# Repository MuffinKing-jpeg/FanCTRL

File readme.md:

# FanCTRL

Yet another fan controller. Has muxing capabilities. Can convert DC input to pwm output or vice versa.  

<center style="font-size: 40px;">WIP</center>

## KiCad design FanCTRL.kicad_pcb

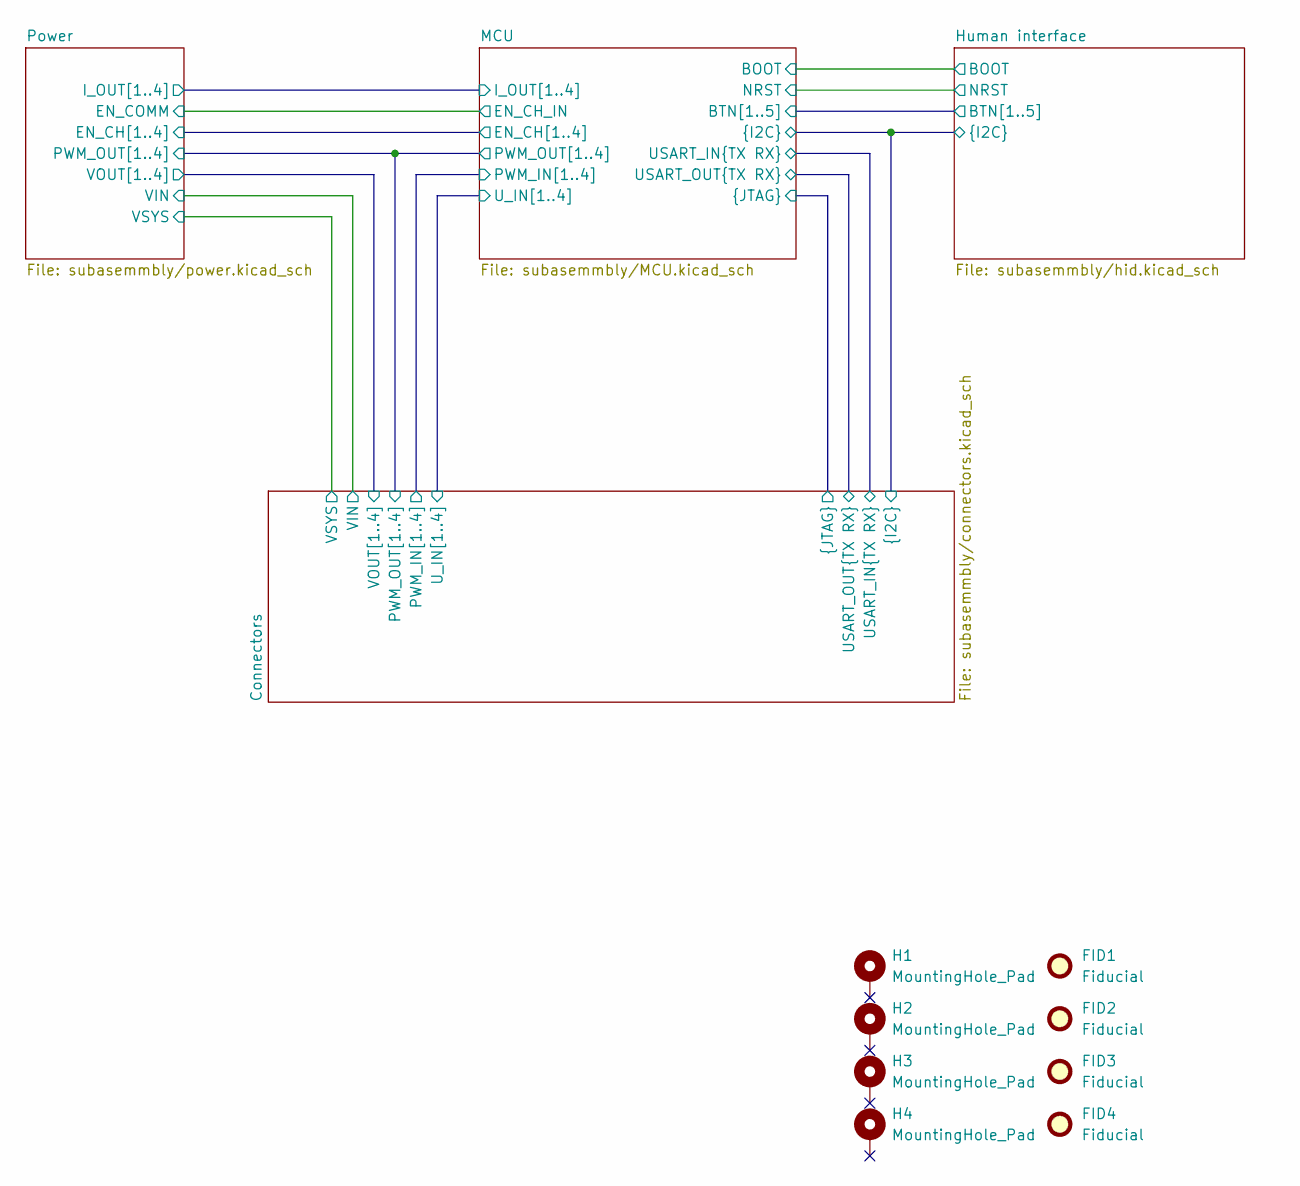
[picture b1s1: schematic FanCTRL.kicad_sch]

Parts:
FID1, FID2, FID3, FID4: Fiducial; Fiducial_1mm_Mask3mm
H1, H2, H3, H4: MountingHole_Pad; MountingHole_3.2mm_M3_ISO7380_Pad

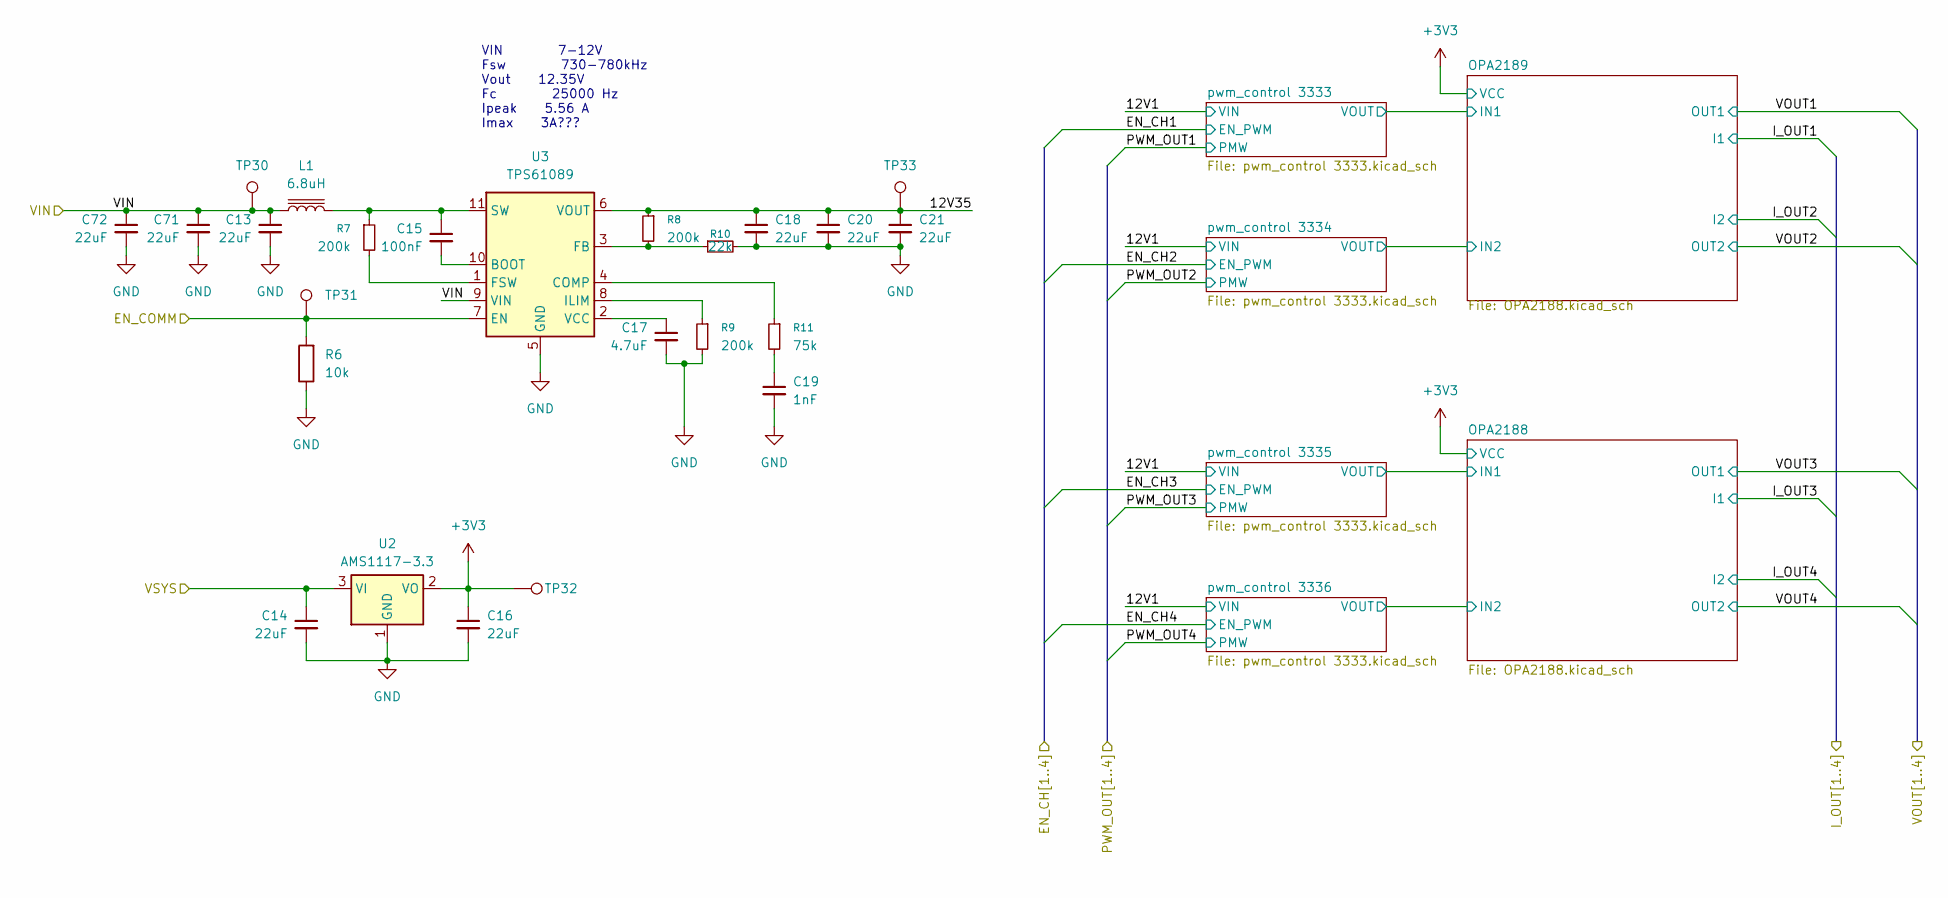
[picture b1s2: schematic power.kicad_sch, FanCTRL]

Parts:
C13, C14, C16, C18, C20, C21, C71, C72: 22uF; C_0805_2012Metric
C15: 100nF; C_0603_1608Metric
C17: 4.7uF; C_0603_1608Metric
C19: 1nF; C_0402_1005Metric
L1: 6.8uH; L_Changjiang_FXL0630; LCSC C167221
R6: 10k; R_0603_1608Metric
R7, R8, R9: 200k; R_0402_1005Metric
R10: 22k; R_0402_1005Metric
R11: 75k; R_0402_1005Metric
TP30: VIN; TestPoint_Pad_D1.0mm
TP31: EN_12V; TestPoint_THTPad_D1.0mm_Drill0.5mm
TP32: 3V3; TestPoint_THTPad_D1.0mm_Drill0.5mm
TP33: 12V35; TestPoint_THTPad_D2.0mm_Drill1.0mm
U2: AMS1117-3.3; SOT-223-3_TabPin2
U3: TPS61089; Texas_VQFN-RNR0011A-11

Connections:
+3V3: C16.1, TP32.1 (1_1), U2.2 (VO); also elsewhere on the board
/Connectors/VIN: C13.1, C71.1, C72.1, L1.1, TP30.1 (1_1), U3.9 (VIN); also elsewhere on the board
/Connectors/VSYS: C14.1, U2.3 (VI); also elsewhere on the board
/MCU/EN_CH_IN: R6.2, TP31.1 (1_1), U3.7 (EN); also elsewhere on the board
/Power/12V35: C18.1, C20.1, C21.1, R8.1, TP33.1 (1_1), U3.6 (VOUT)
GND: C13.2, C14.2, C16.2, C17.2, C18.2, C19.2, C20.2, C21.2, C71.2, C72.2, R6.1, R9.2, R10.2, U2.1 (GND), U3.5 (GND); also elsewhere on the board
unnamed: C19.1, R11.2
unnamed: C15.2, U3.10 (BOOT)
unnamed: R11.1, U3.4 (COMP)
unnamed: R8.2, R10.1, U3.3 (FB)
unnamed: R7.2, U3.1 (FSW)
unnamed: R9.1, U3.8 (ILIM)
unnamed: C15.1, L1.2, R7.1, U3.11 (SW)
unnamed: C17.1, U3.2 (VCC)

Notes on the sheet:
VIN 7-12V Fsw 730-780kHz Vout 12.35V Fc 25000 Hz Ipeak 5.56 A Imax 3A???

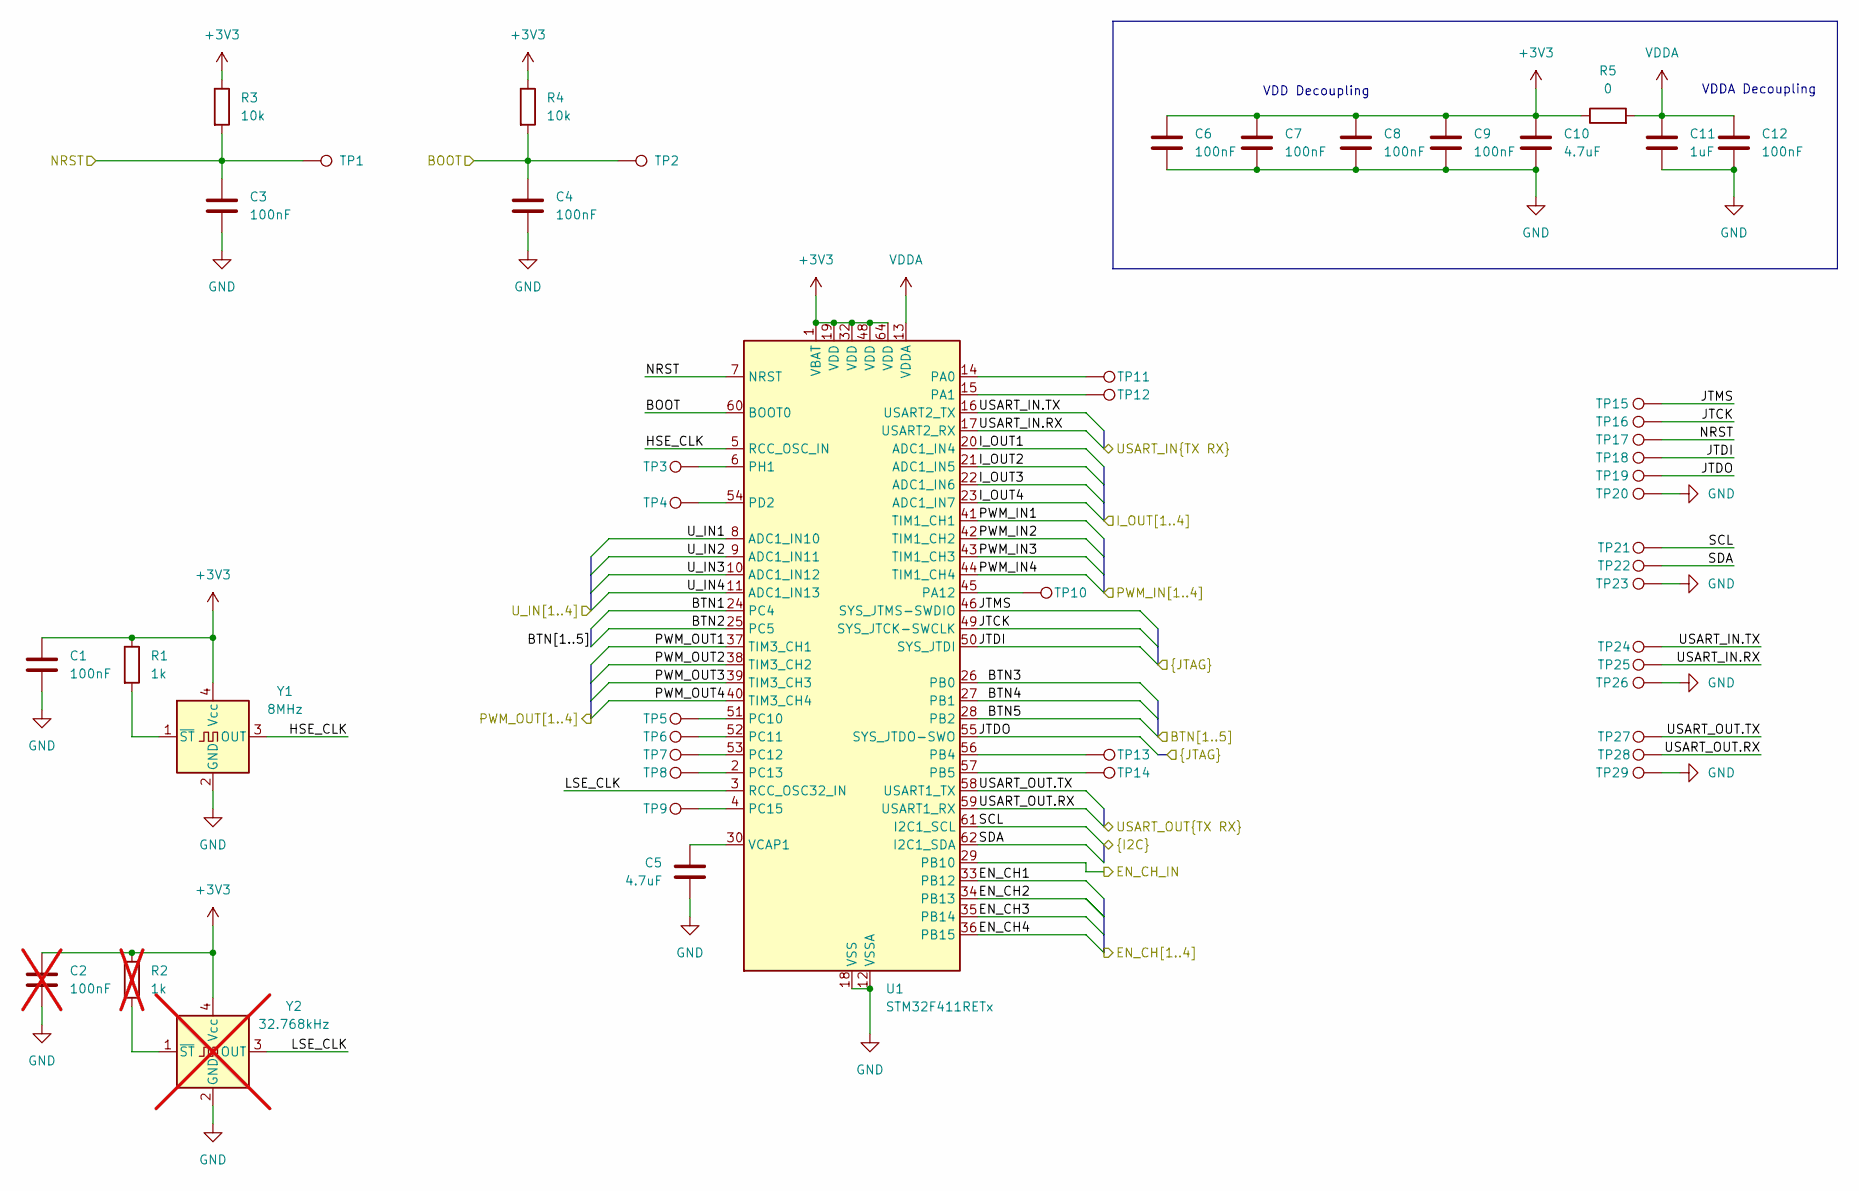
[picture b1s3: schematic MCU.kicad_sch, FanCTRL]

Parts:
C1, C3, C4, C6, C7, C8, C9, C12: 100nF; C_0603_1608Metric
C2: 100nF; C_0603_1608Metric; not fitted
C5, C10: 4.7uF; C_0603_1608Metric
C11: 1uF; C_0603_1608Metric
R1: 1k; R_0603_1608Metric
R2: 1k; R_0603_1608Metric; not fitted
R3, R4: 10k; R_0603_1608Metric
R5: 0; R_0603_1608Metric_Pad0.98x0.95mm_HandSolder
TP1: NRST; TestPoint_THTPad_D1.0mm_Drill0.5mm
TP2: BOOT; TestPoint_THTPad_D1.0mm_Drill0.5mm
TP3, TP4, TP5, TP6, TP7, TP8, TP9, TP10, TP11, TP12, TP13, TP14: TestPoint; TestPoint_THTPad_D1.0mm_Drill0.5mm
TP15: JTMS; TestPoint_Pad_D1.0mm
TP16: JTCK; TestPoint_Pad_D1.0mm
TP17: NRST; TestPoint_Pad_D1.0mm
TP18: JTDI; TestPoint_Pad_D1.0mm
TP19: JTDO; TestPoint_Pad_D1.0mm
TP20: GND; TestPoint_Pad_D1.0mm
TP21: SCL; TestPoint_THTPad_D1.0mm_Drill0.5mm
TP22: SDA; TestPoint_THTPad_D1.0mm_Drill0.5mm
TP23, TP26, TP29: GND; TestPoint_THTPad_D1.0mm_Drill0.5mm
TP24, TP25, TP27, TP28: USART; TestPoint_THTPad_D1.0mm_Drill0.5mm
U1: STM32F411RETx; LQFP-64_10x10mm_P0.5mm
Y1: 8MHz; Oscillator_SMD_SeikoEpson_SG210-4Pin_2.5x2.0mm; LCSC C496696
Y2: 32.768kHz; Oscillator_SMD_SeikoEpson_SG210-4Pin_2.5x2.0mm; LCSC C496696; not fitted

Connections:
+3V3: C1.1, C2.1, C6.1, C7.1, C8.1, C9.1, C10.1, R1.1, R2.1, R3.1, R4.1, R5.1, U1.1 (VBAT), U1.19 (VDD), U1.32 (VDD), U1.48 (VDD), U1.64 (VDD), Y1.4 (Vcc), Y2.4 (Vcc); also elsewhere on the board
/Connectors/JTCK: TP16.1 (1_1), U1.49 (SYS_JTCK-SWCLK); also elsewhere on the board
/Connectors/JTDI: TP18.1 (1_1), U1.50 (SYS_JTDI); also elsewhere on the board
/Connectors/JTDO: TP19.1 (1_1), U1.55 (SYS_JTDO-SWO); also elsewhere on the board
/Connectors/JTMS: TP15.1 (1_1), U1.46 (SYS_JTMS-SWDIO); also elsewhere on the board
/Connectors/PWM_IN1: U1.41 (TIM1_CH1); also elsewhere on the board
/Connectors/PWM_IN2: U1.42 (TIM1_CH2); also elsewhere on the board
/Connectors/PWM_IN3: U1.43 (TIM1_CH3); also elsewhere on the board
/Connectors/PWM_IN4: U1.44 (TIM1_CH4); also elsewhere on the board
/Connectors/PWM_OUT1: U1.37 (TIM3_CH1); also elsewhere on the board
/Connectors/PWM_OUT2: U1.38 (TIM3_CH2); also elsewhere on the board
/Connectors/PWM_OUT3: U1.39 (TIM3_CH3); also elsewhere on the board
/Connectors/PWM_OUT4: U1.40 (TIM3_CH4); also elsewhere on the board
/Connectors/SCL: TP21.1 (1_1), U1.61 (I2C1_SCL); also elsewhere on the board
/Connectors/SDA: TP22.1 (1_1), U1.62 (I2C1_SDA); also elsewhere on the board
/Connectors/USART_IN.RX: TP25.1 (1_1), U1.17 (USART2_RX); also elsewhere on the board
/Connectors/USART_IN.TX: TP24.1 (1_1), U1.16 (USART2_TX); also elsewhere on the board
/Connectors/USART_OUT.RX: TP28.1 (1_1), U1.59 (USART1_RX); also elsewhere on the board
/Connectors/USART_OUT.TX: TP27.1 (1_1), U1.58 (USART1_TX); also elsewhere on the board
/Connectors/U_IN1: U1.8 (ADC1_IN10); also elsewhere on the board
/Connectors/U_IN2: U1.9 (ADC1_IN11); also elsewhere on the board
/Connectors/U_IN3: U1.10 (ADC1_IN12); also elsewhere on the board
/Connectors/U_IN4: U1.11 (ADC1_IN13); also elsewhere on the board
/MCU/BOOT: C4.1, R4.2, TP2.1 (1_1), U1.60 (BOOT0); also elsewhere on the board
/MCU/BTN1: U1.24 (PC4); also elsewhere on the board
/MCU/BTN2: U1.25 (PC5); also elsewhere on the board
/MCU/BTN3: U1.26 (PB0); also elsewhere on the board
/MCU/BTN4: U1.27 (PB1); also elsewhere on the board
/MCU/BTN5: U1.28 (PB2); also elsewhere on the board
/MCU/EN_CH1: U1.33 (PB12); also elsewhere on the board
/MCU/EN_CH2: U1.34 (PB13); also elsewhere on the board
/MCU/EN_CH3: U1.35 (PB14); also elsewhere on the board
/MCU/EN_CH4: U1.36 (PB15); also elsewhere on the board
/MCU/EN_CH_IN: U1.29 (PB10); also elsewhere on the board
/MCU/HSE_CLK: U1.5 (RCC_OSC_IN), Y1.3 (OUT)
/MCU/I_OUT1: U1.20 (ADC1_IN4); also elsewhere on the board
/MCU/I_OUT2: U1.21 (ADC1_IN5); also elsewhere on the board
/MCU/I_OUT3: U1.22 (ADC1_IN6); also elsewhere on the board
/MCU/I_OUT4: U1.23 (ADC1_IN7); also elsewhere on the board
/MCU/LSE_CLK: U1.3 (RCC_OSC32_IN), Y2.3 (OUT)
/MCU/NRST: C3.1, R3.2, TP1.1 (1_1), TP17.1 (1_1), U1.7 (NRST); also elsewhere on the board
GND: C1.2, C2.2, C3.2, C4.2, C5.2, C6.2, C7.2, C8.2, C9.2, C10.2, C11.2, C12.2, TP20.1 (1_1), TP23.1 (1_1), TP26.1 (1_1), TP29.1 (1_1), U1.12 (VSSA), U1.18 (VSS), U1.31 (VSS), U1.47 (VSS), U1.63 (VSS), Y1.2 (GND), Y2.2 (GND); also elsewhere on the board
unnamed: TP11.1 (1_1), U1.14 (PA0)
unnamed: TP12.1 (1_1), U1.15 (PA1)
unnamed: TP10.1 (1_1), U1.45 (PA12)
unnamed: TP13.1 (1_1), U1.56 (PB4)
unnamed: TP14.1 (1_1), U1.57 (PB5)
unnamed: TP5.1 (1_1), U1.51 (PC10)
unnamed: TP6.1 (1_1), U1.52 (PC11)
unnamed: TP7.1 (1_1), U1.53 (PC12)
unnamed: TP8.1 (1_1), U1.2 (PC13)
unnamed: TP9.1 (1_1), U1.4 (PC15)
unnamed: TP4.1 (1_1), U1.54 (PD2)
unnamed: TP3.1 (1_1), U1.6 (PH1)
unnamed: C5.1, U1.30 (VCAP1)
unnamed: R1.2, Y1.1 (~ST)
unnamed: R2.2, Y2.1 (~ST)
VDDA: C11.1, C12.1, R5.2, U1.13 (VDDA)

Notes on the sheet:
VDDA Decoupling
VDD Decoupling

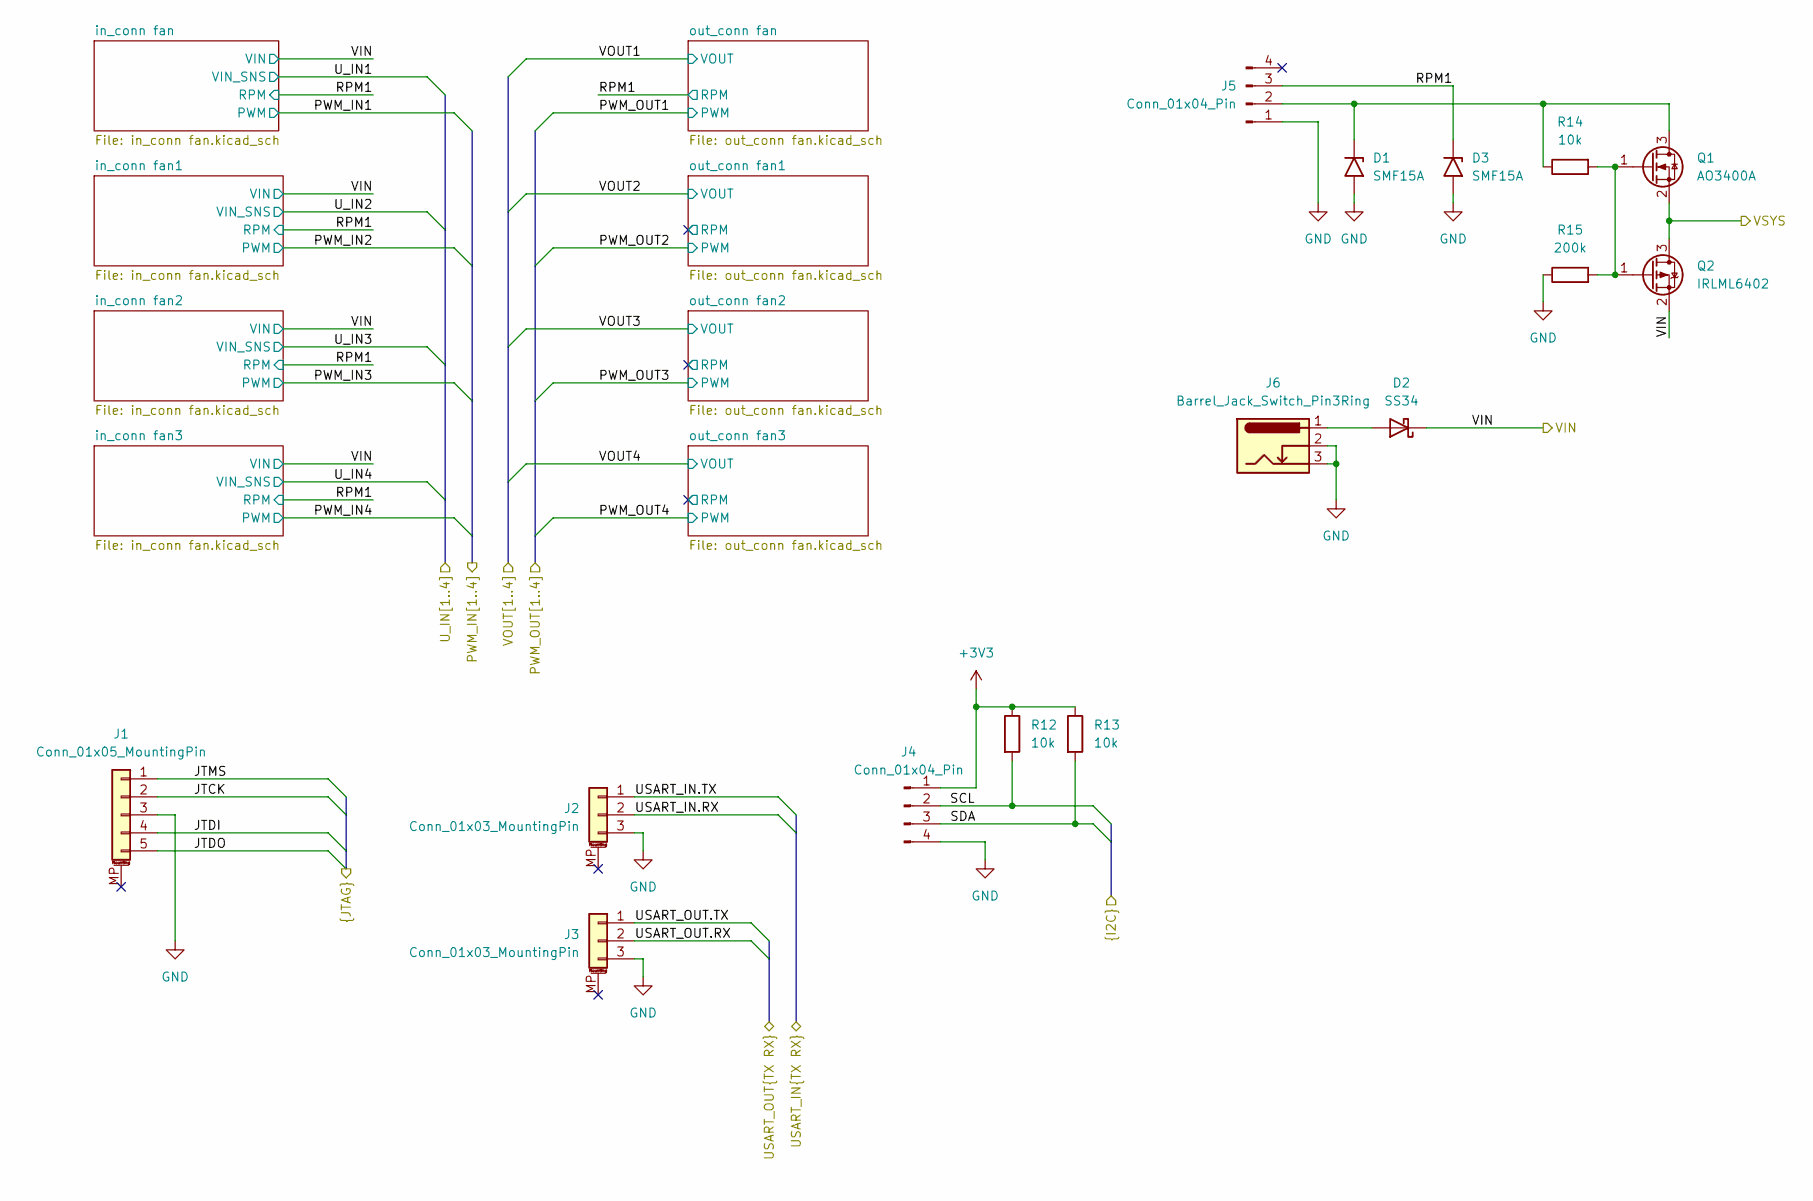
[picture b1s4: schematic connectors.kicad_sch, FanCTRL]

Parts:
D1, D3: SMF15A; D_SMF
D2: SS34; D_SMA
J1: Conn_01x05_MountingPin; Molex_PicoBlade_53261-0571_1x05-1MP_P1.25mm_Horizontal
J2, J3: Conn_01x03_MountingPin; Molex_PicoBlade_53261-0371_1x03-1MP_P1.25mm_Horizontal
J4: Conn_01x04_Pin; JST_EH_S4B-EH_1x04_P2.50mm_Horizontal
J5: Conn_01x04_Pin; FanPinHeader_1x04_P2.54mm_Vertical
J6: Barrel_Jack_Switch_Pin3Ring; BarrelJack_GCT_DCJ200-10-A_Horizontal
Q1: AO3400A; SOT-23
Q2: IRLML6402; SOT-23
R12, R13, R14: 10k; R_0603_1608Metric
R15: 200k; R_0402_1005Metric

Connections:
+3V3: J4.1, R12.1, R13.1; also elsewhere on the board
/Connectors/JTCK: J1.2; also elsewhere on the board
/Connectors/JTDI: J1.4; also elsewhere on the board
/Connectors/JTDO: J1.5; also elsewhere on the board
/Connectors/JTMS: J1.1; also elsewhere on the board
/Connectors/RPM1: D3.1 (A1), J5.3; also elsewhere on the board
/Connectors/SCL: J4.2, R12.2; also elsewhere on the board
/Connectors/SDA: J4.3, R13.2; also elsewhere on the board
/Connectors/USART_IN.RX: J2.2; also elsewhere on the board
/Connectors/USART_IN.TX: J2.1; also elsewhere on the board
/Connectors/USART_OUT.RX: J3.2; also elsewhere on the board
/Connectors/USART_OUT.TX: J3.1; also elsewhere on the board
/Connectors/VIN: D2.1 (K), Q2.2 (S); also elsewhere on the board
/Connectors/VSYS: Q1.2 (S), Q2.3 (D); also elsewhere on the board
GND: D1.2 (A2), D3.2 (A2), J1.3, J2.3, J3.3, J4.4, J5.1, J6.2, J6.3, R15.1; also elsewhere on the board
unnamed: D1.1 (A1), J5.2, Q1.3 (D), R14.1
unnamed: D2.2 (A), J6.1
unnamed: Q1.1 (G), Q2.1 (G), R14.2, R15.2

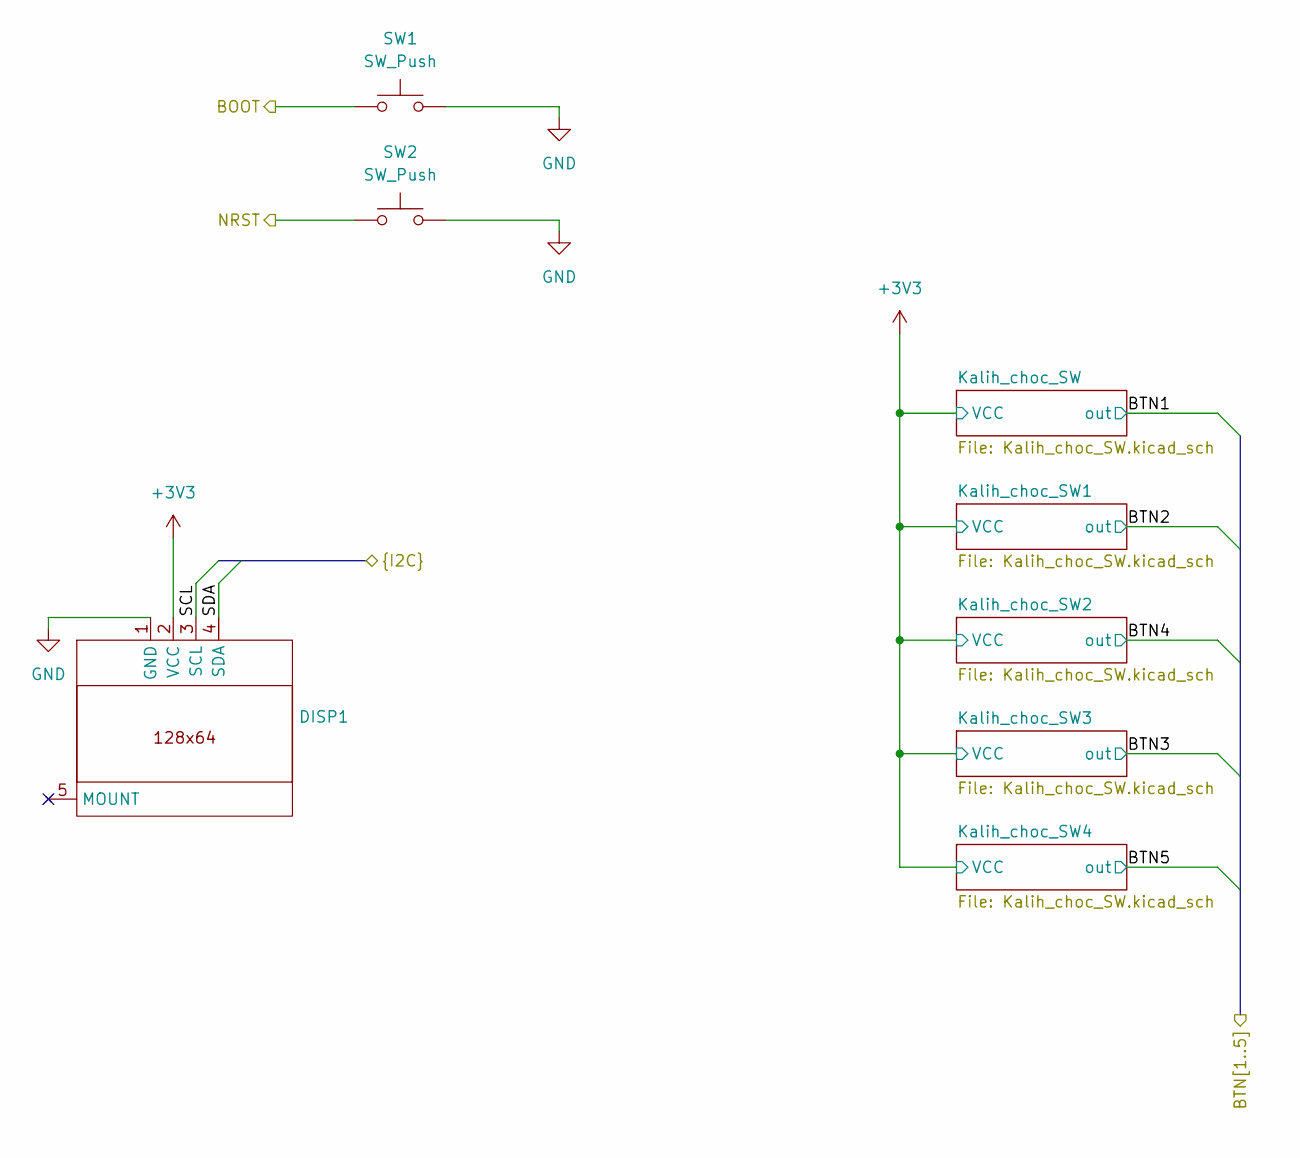
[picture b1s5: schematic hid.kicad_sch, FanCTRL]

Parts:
DISP1: OLED_Module_I2C_WeAct
SW1, SW2: SW_Push; SW_SPST_PTS810

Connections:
+3V3: DISP1.2 (VCC); also elsewhere on the board
/Connectors/SCL: DISP1.3 (SCL); also elsewhere on the board
/Connectors/SDA: DISP1.4 (SDA); also elsewhere on the board
/MCU/BOOT: SW1.1; also elsewhere on the board
/MCU/NRST: SW2.1; also elsewhere on the board
GND: DISP1.1 (GND), SW1.2, SW2.2; also elsewhere on the board

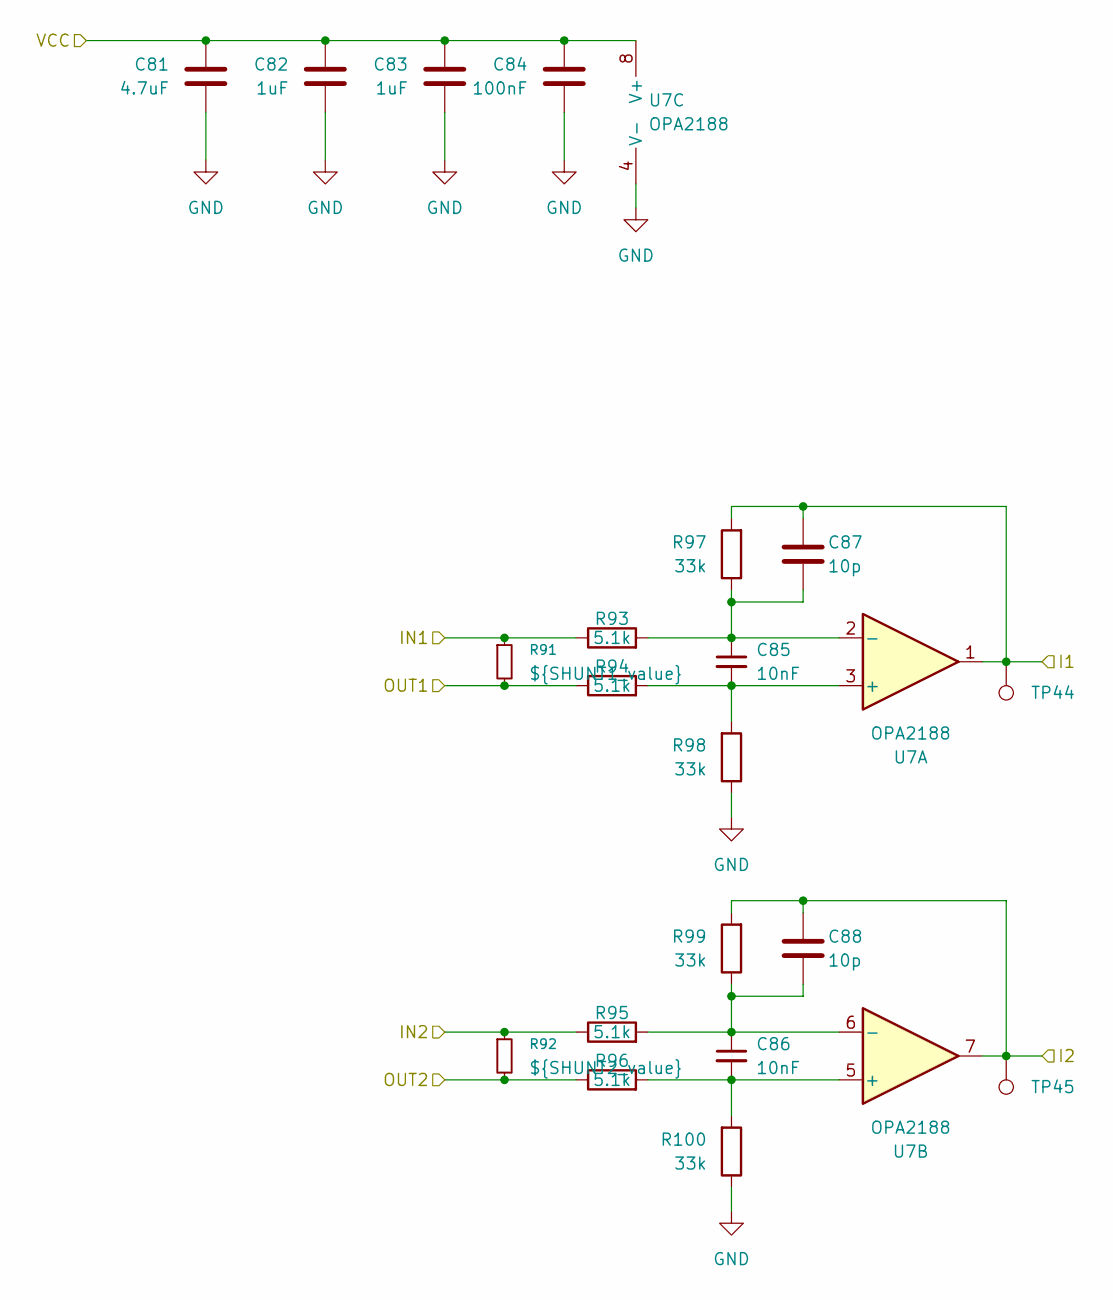
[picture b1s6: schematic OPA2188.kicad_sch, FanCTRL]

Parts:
C81: 4.7uF; C_0603_1608Metric
C82, C83: 1uF; C_0603_1608Metric
C84: 100nF; C_0603_1608Metric
C85, C86: 10nF; C_0402_1005Metric
C87, C88: 10p; C_0402_1005Metric
R91: ${SHUNT1_value}; R_2512_6332Metric; LCSC C49164952
R92: ${SHUNT2_value}; R_2512_6332Metric; LCSC C49164952
R93, R94, R95, R96: 5.1k; R_0402_1005Metric
R97, R98, R99, R100: 33k; R_0402_1005Metric
TP44, TP45: I_OUT; TestPoint_Pad_D1.0mm
U7: OPA2188; SOIC-8_3.9x4.9mm_P1.27mm

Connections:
+3V3: C81.1, C82.1, C83.1, C84.1, U7.8 (V+); also elsewhere on the board
/Connectors/VOUT1: R91.2, R94.1; also elsewhere on the board
/Connectors/VOUT2: R92.2, R96.1; also elsewhere on the board
/MCU/I_OUT1: C87.1, R97.2, TP44.1 (1_1), U7.1; also elsewhere on the board
/MCU/I_OUT2: C88.1, R99.2, TP45.1 (1_1), U7.7; also elsewhere on the board
/Power/OPA2189/IN1: R91.1, R93.1; also elsewhere on the board
/Power/OPA2189/IN2: R92.1, R95.1; also elsewhere on the board
GND: C81.2, C82.2, C83.2, C84.2, R98.1, R100.1, U7.4 (V-); also elsewhere on the board
unnamed: C85.2, R94.2, R98.2, U7.3 (+)
unnamed: C85.1, C87.2, R93.2, R97.1, U7.2 (-)
unnamed: C86.2, R96.2, R100.2, U7.5 (+)
unnamed: C86.1, C88.2, R95.2, R99.1, U7.6 (-)

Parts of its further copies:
C73: 4.7uF; C_0603_1608Metric
C74, C75: 1uF; C_0603_1608Metric
C76: 100nF; C_0603_1608Metric
C77, C78: 10nF; C_0402_1005Metric
C79, C80: 10p; C_0402_1005Metric
R83, R84, R85, R86: 5.1k; R_0402_1005Metric
R87, R88, R89, R90: 33k; R_0402_1005Metric
TP42, TP43: I_OUT; TestPoint_Pad_D1.0mm
U6: OPA2188; SOIC-8_3.9x4.9mm_P1.27mm

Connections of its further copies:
+3V3: C73.1, C74.1, C75.1, C76.1, U6.8 (V+); also elsewhere on the board
/Connectors/VOUT3: R84.1; also elsewhere on the board
/Connectors/VOUT4: R86.1; also elsewhere on the board
/MCU/I_OUT3: C79.1, R87.2, TP42.1 (1_1), U6.1; also elsewhere on the board
/MCU/I_OUT4: C80.1, R89.2, TP43.1 (1_1), U6.7; also elsewhere on the board
/Power/OPA2188/IN1: R83.1; also elsewhere on the board
/Power/OPA2188/IN2: R85.1; also elsewhere on the board
GND: C73.2, C74.2, C75.2, C76.2, R88.1, R90.1, U6.4 (V-); also elsewhere on the board
unnamed: C77.2, R84.2, R88.2, U6.3 (+)
unnamed: C77.1, C79.2, R83.2, R87.1, U6.2 (-)
unnamed: C78.2, R86.2, R90.2, U6.5 (+)
unnamed: C78.1, C80.2, R85.2, R89.1, U6.6 (-)

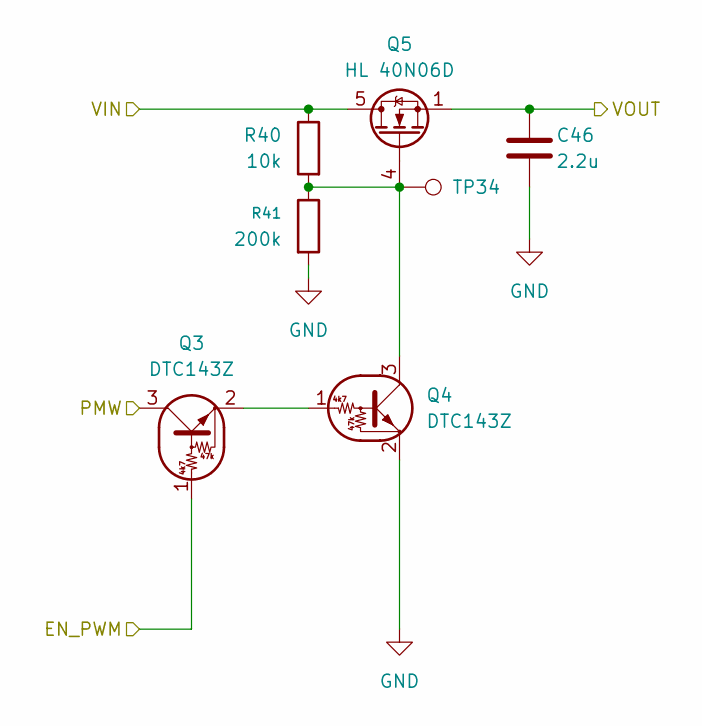
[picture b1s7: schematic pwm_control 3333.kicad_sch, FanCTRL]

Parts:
C46: 2.2u; C_0603_1608Metric
Q3, Q4: DTC143Z; SC-59
Q5: HL 40N06D; PowerDI3333-8; LCSC C7543836
R40: 10k; R_0603_1608Metric
R41: 200k; R_0402_1005Metric
TP34: OUT_GATE; TestPoint_Pad_D1.0mm

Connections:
/Connectors/PWM_OUT1: Q3.3 (C); also elsewhere on the board
/MCU/EN_CH1: Q3.1 (B); also elsewhere on the board
/Power/12V1: Q5.5 (D), R40.1; also elsewhere on the board
/Power/OPA2189/IN1: C46.1, Q5.1 (S), Q5.2 (S), Q5.3 (S); also elsewhere on the board
GND: C46.2, Q4.2 (E), R41.2; also elsewhere on the board
unnamed: Q3.2 (E), Q4.1 (B)
unnamed: Q4.3 (C), Q5.4 (G), R40.2, R41.1, TP34.1 (1_1)

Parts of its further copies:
C47, C48, C49: 2.2u; C_0603_1608Metric
Q6, Q7, Q9, Q10, Q12, Q13: DTC143Z; SC-59
Q8, Q11, Q14: HL 40N06D; PowerDI3333-8; LCSC C7543836
R42, R44, R46: 10k; R_0603_1608Metric
R43, R45, R47: 200k; R_0402_1005Metric
TP35, TP36, TP37: OUT_GATE; TestPoint_Pad_D1.0mm

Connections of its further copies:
/Connectors/PWM_OUT2: Q6.3 (C); also elsewhere on the board
/Connectors/PWM_OUT3: Q9.3 (C); also elsewhere on the board
/Connectors/PWM_OUT4: Q12.3 (C); also elsewhere on the board
/MCU/EN_CH2: Q6.1 (B); also elsewhere on the board
/MCU/EN_CH3: Q9.1 (B); also elsewhere on the board
/MCU/EN_CH4: Q12.1 (B); also elsewhere on the board
/Power/12V1: Q8.5 (D), Q11.5 (D), Q14.5 (D), R42.1, R44.1, R46.1; also elsewhere on the board
/Power/OPA2188/IN1: C48.1, Q11.1 (S), Q11.2 (S), Q11.3 (S); also elsewhere on the board
/Power/OPA2188/IN2: C49.1, Q14.1 (S), Q14.2 (S), Q14.3 (S); also elsewhere on the board
/Power/OPA2189/IN2: C47.1, Q8.1 (S), Q8.2 (S), Q8.3 (S); also elsewhere on the board
GND: C47.2, C48.2, C49.2, Q7.2 (E), Q10.2 (E), Q13.2 (E), R43.2, R45.2, R47.2; also elsewhere on the board
unnamed: Q6.2 (E), Q7.1 (B)
unnamed: Q7.3 (C), Q8.4 (G), R42.2, R43.1, TP35.1 (1_1)
unnamed: Q9.2 (E), Q10.1 (B)
unnamed: Q10.3 (C), Q11.4 (G), R44.2, R45.1, TP36.1 (1_1)
unnamed: Q12.2 (E), Q13.1 (B)
unnamed: Q13.3 (C), Q14.4 (G), R46.2, R47.1, TP37.1 (1_1)

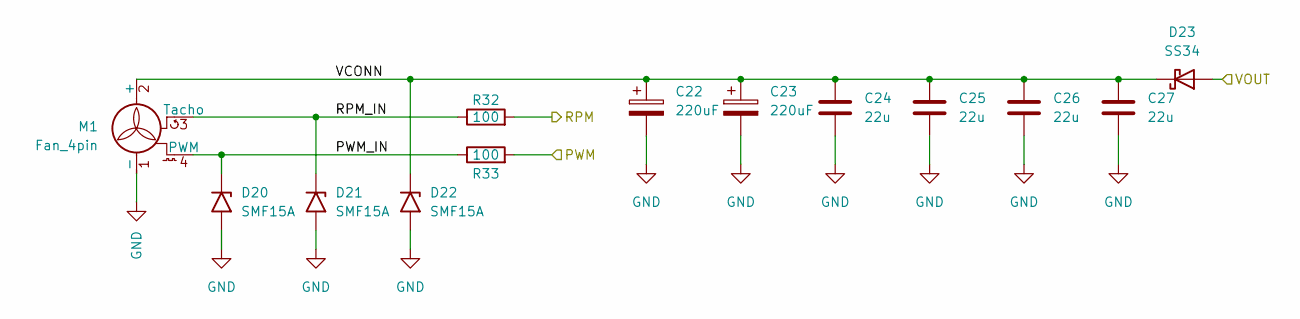
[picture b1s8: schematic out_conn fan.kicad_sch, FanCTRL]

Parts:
C22, C23: 220uF; CP_Radial_D8.0mm_P2.50mm; LCSC C107639
C24, C25, C26, C27: 22u; C_0805_2012Metric
D20, D21, D22: SMF15A; D_SMF
D23: SS34; D_SMA
M1: Fan_4pin; FanPinHeader_1x04_P2.54mm_Vertical
R32, R33: 100; R_0603_1608Metric

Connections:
/Connectors/PWM_OUT1: R33.2; also elsewhere on the board
/Connectors/RPM1: R32.2; also elsewhere on the board
/Connectors/VOUT1: D23.2 (A); also elsewhere on the board
/Connectors/out_conn fan/PWM_IN: D20.1 (A1), M1.4 (PWM), R33.1
/Connectors/out_conn fan/RPM_IN: D21.1 (A1), M1.3 (Tacho), R32.1
/Connectors/out_conn fan/VCONN: C22.1, C23.1, C24.1, C25.1, C26.1, C27.1, D22.1 (A1), D23.1 (K), M1.2 (+)
GND: C22.2, C23.2, C24.2, C25.2, C26.2, C27.2, D20.2 (A2), D21.2 (A2), D22.2 (A2), M1.1 (-); also elsewhere on the board

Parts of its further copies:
C28, C29, C34, C35, C40, C41: 220uF; CP_Radial_D8.0mm_P2.50mm; LCSC C107639
C30, C31, C32, C33, C36, C37, C38, C39, C42, C43, C44, C45: 22u; C_0805_2012Metric
D24, D25, D26, D28, D29, D30, D32, D33, D34: SMF15A; D_SMF
D27, D31, D35: SS34; D_SMA
M2, M3, M4: Fan_4pin; FanPinHeader_1x04_P2.54mm_Vertical
R34, R35, R36, R37, R38, R39: 100; R_0603_1608Metric

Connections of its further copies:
/Connectors/PWM_OUT2: R35.2; also elsewhere on the board
/Connectors/PWM_OUT3: R37.2; also elsewhere on the board
/Connectors/PWM_OUT4: R39.2; also elsewhere on the board
/Connectors/VOUT2: D27.2 (A); also elsewhere on the board
/Connectors/VOUT3: D31.2 (A); also elsewhere on the board
/Connectors/VOUT4: D35.2 (A); also elsewhere on the board
/Connectors/out_conn fan1/PWM_IN: D24.1 (A1), M2.4 (PWM), R35.1
/Connectors/out_conn fan1/RPM: R34.2
/Connectors/out_conn fan1/RPM_IN: D25.1 (A1), M2.3 (Tacho), R34.1
/Connectors/out_conn fan1/VCONN: C28.1, C29.1, C30.1, C31.1, C32.1, C33.1, D26.1 (A1), D27.1 (K), M2.2 (+)
/Connectors/out_conn fan2/PWM_IN: D28.1 (A1), M3.4 (PWM), R37.1
/Connectors/out_conn fan2/RPM: R36.2
/Connectors/out_conn fan2/RPM_IN: D29.1 (A1), M3.3 (Tacho), R36.1
/Connectors/out_conn fan2/VCONN: C34.1, C35.1, C36.1, C37.1, C38.1, C39.1, D30.1 (A1), D31.1 (K), M3.2 (+)
/Connectors/out_conn fan3/PWM_IN: D32.1 (A1), M4.4 (PWM), R39.1
/Connectors/out_conn fan3/RPM: R38.2
/Connectors/out_conn fan3/RPM_IN: D33.1 (A1), M4.3 (Tacho), R38.1
/Connectors/out_conn fan3/VCONN: C40.1, C41.1, C42.1, C43.1, C44.1, C45.1, D34.1 (A1), D35.1 (K), M4.2 (+)
GND: C28.2, C29.2, C30.2, C31.2, C32.2, C33.2, C34.2, C35.2, C36.2, C37.2, C38.2, C39.2, C40.2, C41.2, C42.2, C43.2, C44.2, C45.2, D24.2 (A2), D25.2 (A2), D26.2 (A2), D28.2 (A2), D29.2 (A2), D30.2 (A2), D32.2 (A2), D33.2 (A2), D34.2 (A2), M2.1 (-), M3.1 (-), M4.1 (-); also elsewhere on the board

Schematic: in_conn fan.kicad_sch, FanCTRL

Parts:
D4, D5, D6: SMF15A; D_SMF
D7: SS34; D_SMA
J7: Conn_01x04_Pin; FanPinHeader_1x04_P2.54mm_Vertical
R16: 75k; R_0402_1005Metric
R17: 22k; R_0402_1005Metric
R18, R19: 100; R_0603_1608Metric

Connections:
/Connectors/PWM_IN1: R19.2; also elsewhere on the board
/Connectors/RPM1: R18.2; also elsewhere on the board
/Connectors/U_IN1: R16.2, R17.1; also elsewhere on the board
/Connectors/VIN: D7.1 (K); also elsewhere on the board
/Connectors/in_conn fan/PWM_IN: D4.1 (A1), J7.4, R19.1
/Connectors/in_conn fan/RPM_IN: D5.1 (A1), J7.3, R18.1
/Connectors/in_conn fan/VCONN: D6.1 (A1), D7.2 (A), J7.2, R16.1
GND: D4.2 (A2), D5.2 (A2), D6.2 (A2), J7.1, R17.2; also elsewhere on the board

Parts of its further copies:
D8, D9, D10, D12, D13, D14, D16, D17, D18: SMF15A; D_SMF
D11, D15, D19: SS34; D_SMA
J8, J9, J10: Conn_01x04_Pin; FanPinHeader_1x04_P2.54mm_Vertical
R20, R24, R28: 75k; R_0402_1005Metric
R21, R25, R29: 22k; R_0402_1005Metric
R22, R23, R26, R27, R30, R31: 100; R_0603_1608Metric

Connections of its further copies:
/Connectors/PWM_IN2: R23.2; also elsewhere on the board
/Connectors/PWM_IN3: R27.2; also elsewhere on the board
/Connectors/PWM_IN4: R31.2; also elsewhere on the board
/Connectors/RPM1: R22.2, R26.2, R30.2; also elsewhere on the board
/Connectors/U_IN2: R20.2, R21.1; also elsewhere on the board
/Connectors/U_IN3: R24.2, R25.1; also elsewhere on the board
/Connectors/U_IN4: R28.2, R29.1; also elsewhere on the board
/Connectors/VIN: D11.1 (K), D15.1 (K), D19.1 (K); also elsewhere on the board
/Connectors/in_conn fan1/PWM_IN: D8.1 (A1), J8.4, R23.1
/Connectors/in_conn fan1/RPM_IN: D9.1 (A1), J8.3, R22.1
/Connectors/in_conn fan1/VCONN: D10.1 (A1), D11.2 (A), J8.2, R20.1
/Connectors/in_conn fan2/PWM_IN: D12.1 (A1), J9.4, R27.1
/Connectors/in_conn fan2/RPM_IN: D13.1 (A1), J9.3, R26.1
/Connectors/in_conn fan2/VCONN: D14.1 (A1), D15.2 (A), J9.2, R24.1
/Connectors/in_conn fan3/PWM_IN: D16.1 (A1), J10.4, R31.1
/Connectors/in_conn fan3/RPM_IN: D17.1 (A1), J10.3, R30.1
/Connectors/in_conn fan3/VCONN: D18.1 (A1), D19.2 (A), J10.2, R28.1
GND: D8.2 (A2), D9.2 (A2), D10.2 (A2), D12.2 (A2), D13.2 (A2), D14.2 (A2), D16.2 (A2), D17.2 (A2), D18.2 (A2), J8.1, J9.1, J10.1, R21.2, R25.2, R29.2; also elsewhere on the board

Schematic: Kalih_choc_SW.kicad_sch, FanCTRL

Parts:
C50: 100nF; C_0603_1608Metric
R48: 10k; R_0603_1608Metric
SW3: SW_Push; SW_Kailh_Choc_V1V2_1.00u

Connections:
+3V3: R48.1; also elsewhere on the board
/MCU/BTN1: SW3.1; also elsewhere on the board
GND: C50.2; also elsewhere on the board
unnamed: C50.1, R48.2, SW3.2

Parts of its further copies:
C51, C52, C53, C54: 100nF; C_0603_1608Metric
R49, R50, R51, R52: 10k; R_0603_1608Metric
SW4, SW5, SW6, SW7: SW_Push; SW_Kailh_Choc_V1V2_1.00u

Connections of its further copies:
+3V3: R49.1, R50.1, R51.1, R52.1; also elsewhere on the board
/MCU/BTN2: SW4.1; also elsewhere on the board
/MCU/BTN3: SW6.1; also elsewhere on the board
/MCU/BTN4: SW5.1; also elsewhere on the board
/MCU/BTN5: SW7.1; also elsewhere on the board
GND: C51.2, C52.2, C53.2, C54.2; also elsewhere on the board
unnamed: C51.1, R49.2, SW4.2
unnamed: C52.1, R50.2, SW5.2
unnamed: C53.1, R51.2, SW6.2
unnamed: C54.1, R52.2, SW7.2
